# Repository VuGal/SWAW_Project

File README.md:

# SWAW_Project
Weather station project for SWAW course.

Android directory - contains the source code of the Android app which fetches the weather info from the server (along with prediction data)

Azure directory - contains the scripts related to weather prediction and database operations

Nucleo directory - contains the STM32 Nucleo source code (based on STM32CubeIDE) which is responsible for the communication with sensors and CAN communication with Raspberry Pi

PCB - contains the files related to the PCBs created for the project

Raspberry Pi - contains the Python scripts which are responsible for fetching the weather info via CAN bus and sending it to the server

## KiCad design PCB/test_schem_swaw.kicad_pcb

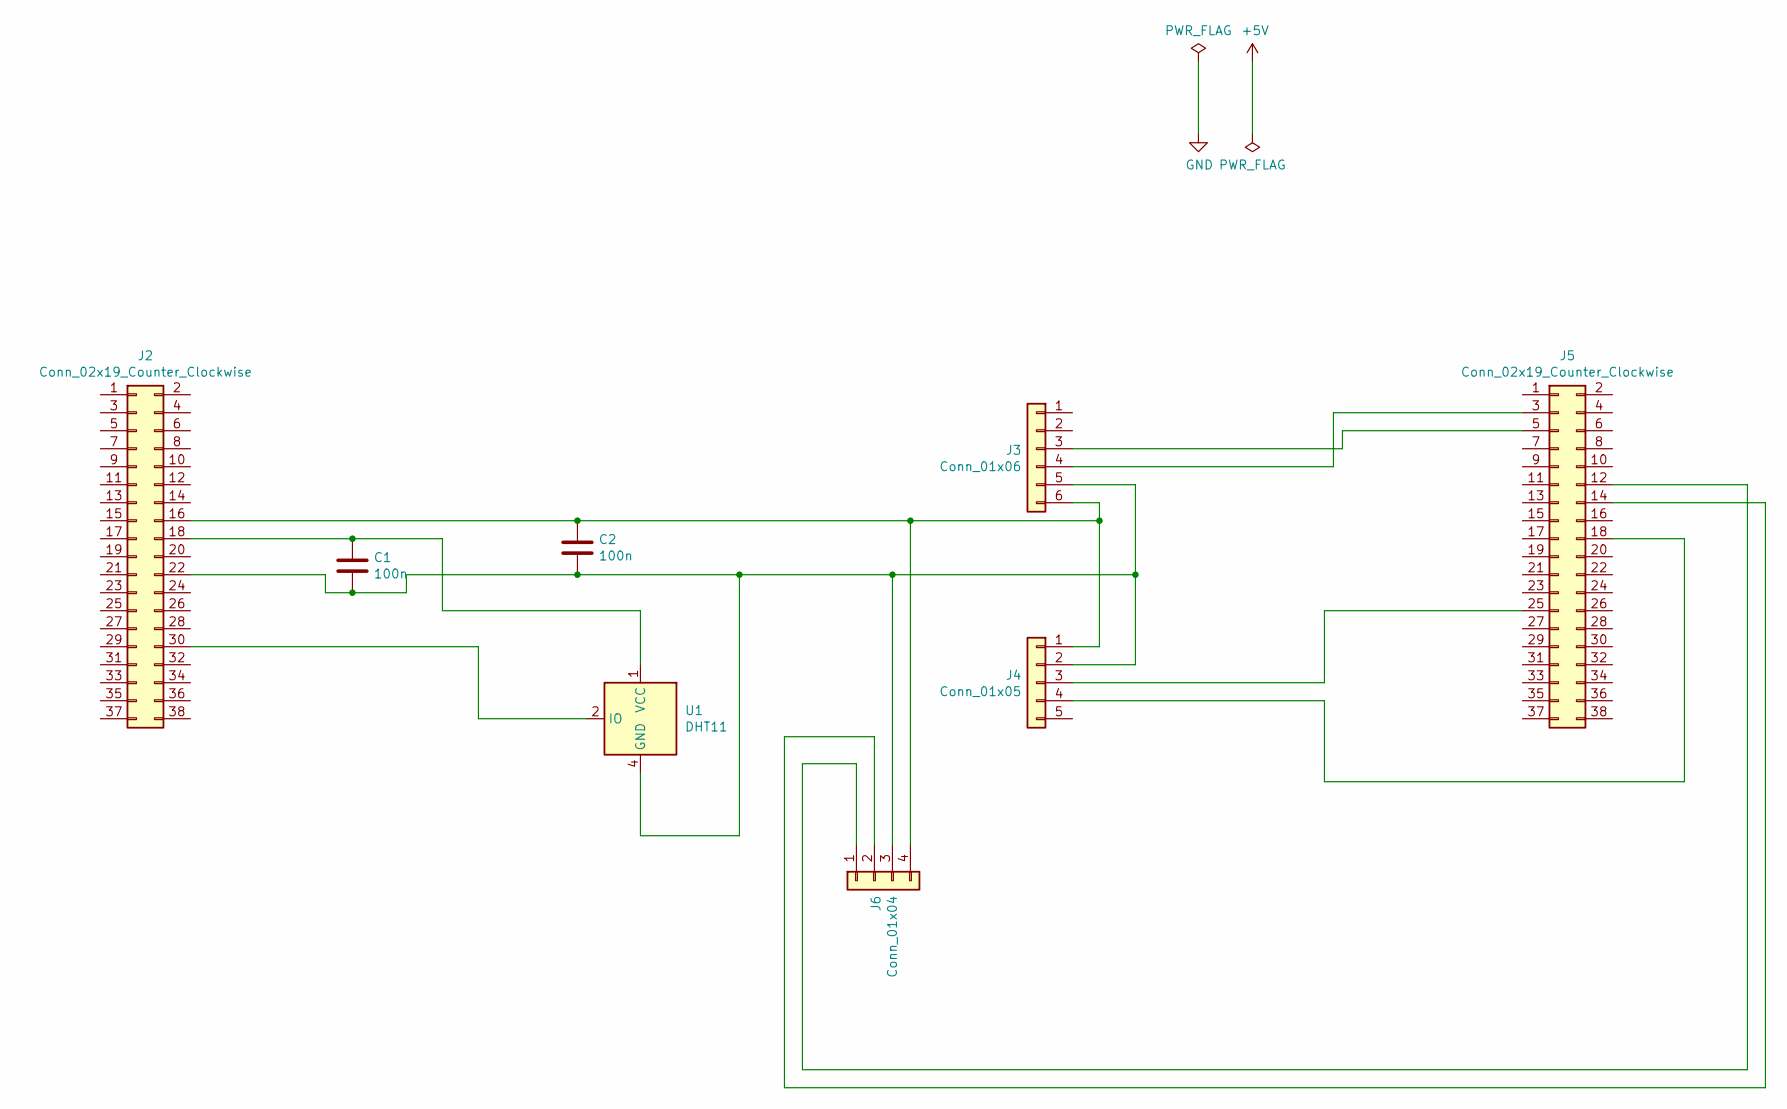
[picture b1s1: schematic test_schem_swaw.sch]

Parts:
C1, C2: 100n; C_Disc_D7.5mm_W4.4mm_P5.00mm
J2, J5: Conn_02x19_Counter_Clockwise; PinSocket_2x19_P2.54mm_Vertical
J3: Conn_01x06; PinSocket_1x06_P2.54mm_Vertical
J4: Conn_01x05; PinSocket_1x05_P2.54mm_Vertical
J6: Conn_01x04; PinSocket_1x04_P2.54mm_Vertical
U1: DHT11; Aosong_DHT11_5.5x12.0_P2.54mm

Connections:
unnamed: C1.1, J2.18, U1.1 (VCC)
unnamed: C1.2, C2.2, J2.22, J3.5, J4.2, J6.3, U1.4 (GND)
unnamed: C2.1, J2.16, J3.6, J4.1, J6.4
unnamed: J2.30, U1.2 (IO)
unnamed: J3.3, J5.5
unnamed: J3.4, J5.3
unnamed: J4.3, J5.25
unnamed: J4.4, J5.18
unnamed: J5.12, J6.1
unnamed: J5.14, J6.2

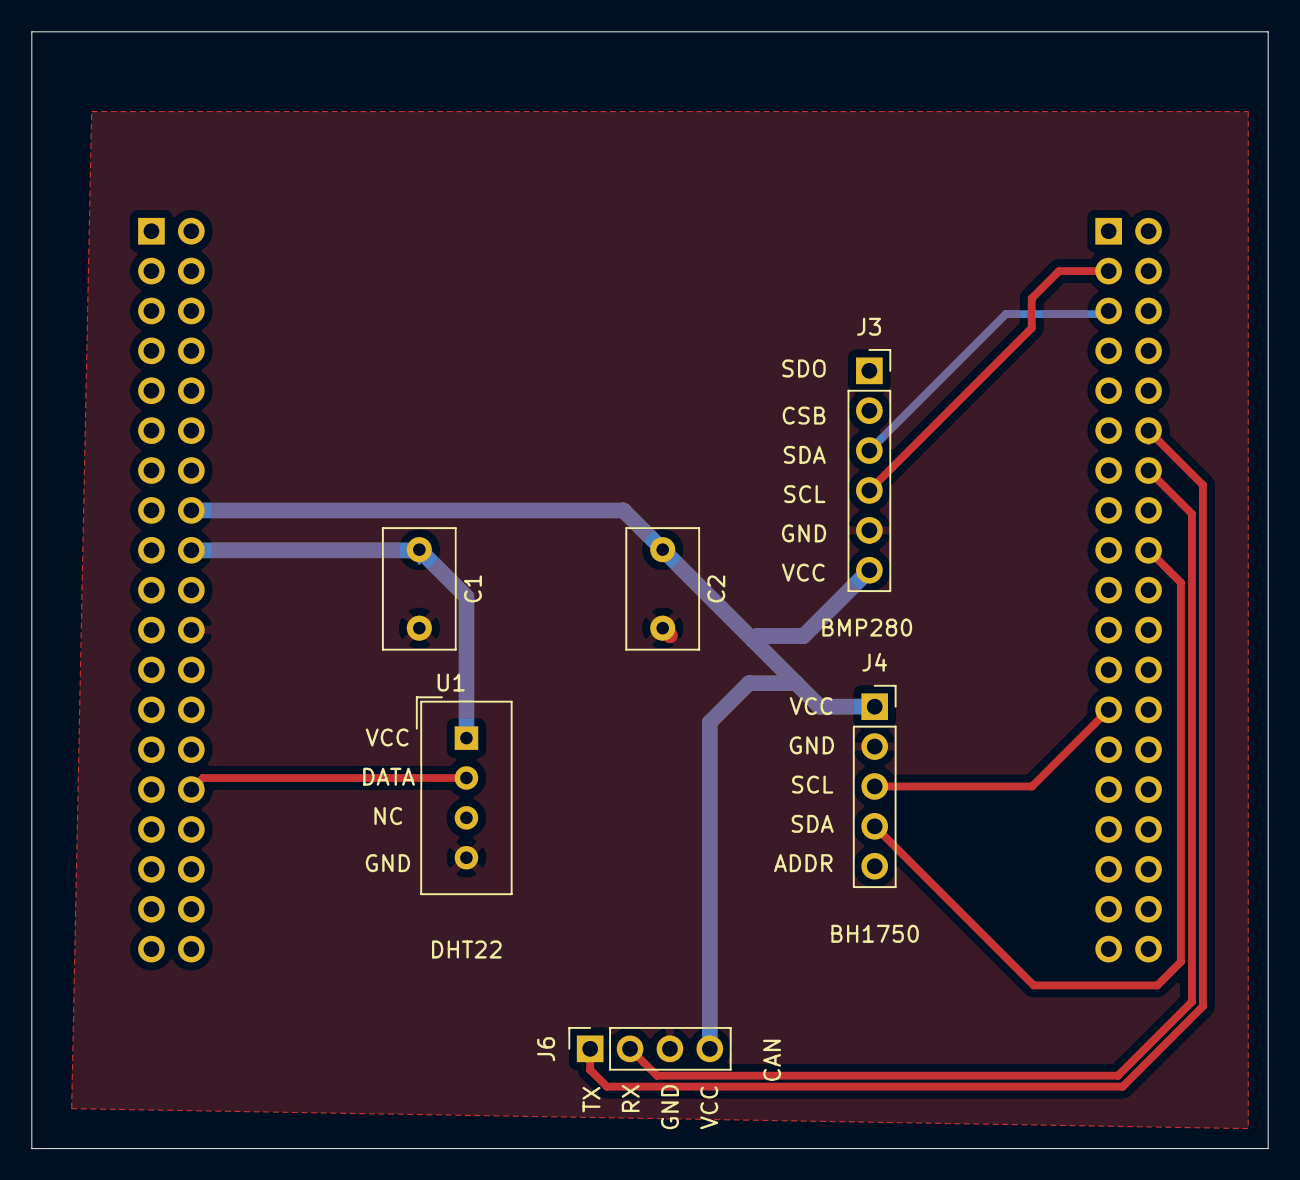
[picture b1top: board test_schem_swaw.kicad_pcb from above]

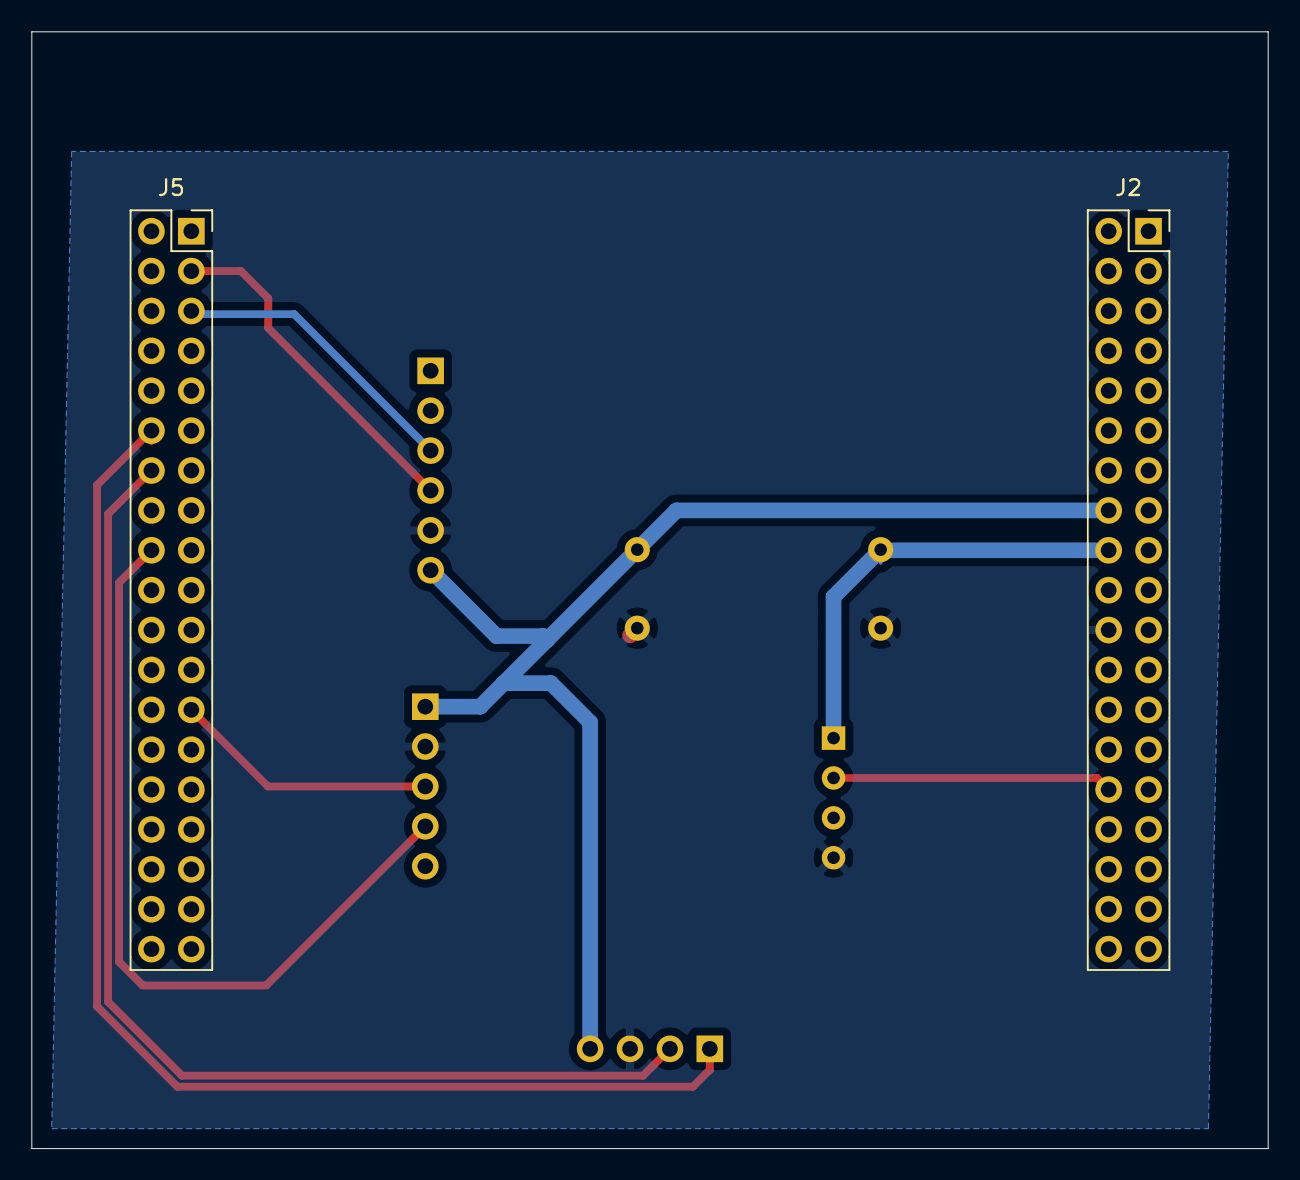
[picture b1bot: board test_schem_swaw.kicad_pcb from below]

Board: 4 copper layers, 78.7 x 71.1 mm, 8 parts (2 on the bottom side), 10 nets.

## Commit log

2021-03-20 Nucleo project skeleton
2021-03-24 Create Git repository structure
2021-03-29 Add run_oled.py file
2021-04-10 Basic Android application
    The app scraps the weather data from index.html located on the server.
2021-04-15 Add update_data.py file
2021-04-22 Add PCB schematics
2021-05-01 DHT22 sensor working
2021-06-03 Updated version of Raspberry Pi Python scripts
2021-06-03 Full Nucleo application
    Includes handling of all three sensors (DHT22, BMP280, BH1750) and
    working CAN bus transmission.
2021-06-03 Modified scheme of PCB - final version, not developed anymore
2021-06-03 Add save_history.py file
2021-06-04 Add script with prediction and classification
    The weather forecast for the following day is calculated with usage of data from previous twenty days. Determines whether precipitation will occur or not .
2021-06-04 Add prediction calculation after every update.
    Every update of database trigger another prediction calculation.
2021-06-04 Repair function naming
2021-06-04 Add prediction activity to WeatherStation app
2021-06-04 Fix prediction
